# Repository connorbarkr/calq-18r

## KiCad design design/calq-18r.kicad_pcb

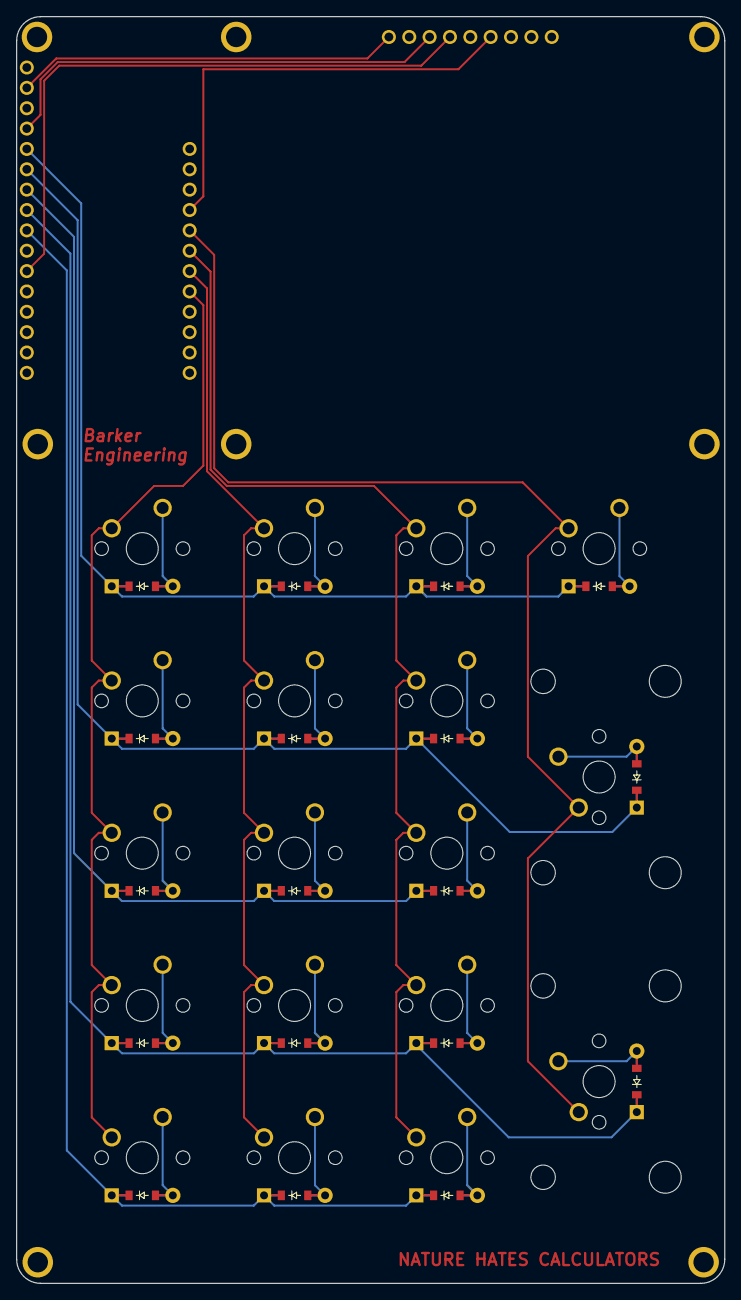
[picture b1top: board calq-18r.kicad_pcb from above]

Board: 2 copper layers, 88.4 x 158.1 mm, 40 parts (0 on the bottom side), 31 nets.

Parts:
D1, D2, D3, D4, D5, D6, D7, D8, D9, D10, D11, D12, D13, D14, D15, D16, D17, D18: ComboDiode
DISP1: DISP; SHARP_2_7
MCU1: Feather_nRF52840
S1, S2, S3, S4, S5, S6, S7, S8, S9, S10, S11, S12, S13, S14, S15, S16, S17, S18: MX
Stab1, Stab2: MX_stabilizer

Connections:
A0: D5.1, D5.2, D10.1, D10.2, D15.1, D15.2, D18.1, D18.2, MCU1.17
A1: D4.1, D4.2, D9.1, D9.2, D14.1, D14.2, D17.1, D17.2, MCU1.18
A2: D3.1, D3.2, D8.1, D8.2, D13.1, D13.2, MCU1.19
A3: D2.1, D2.2, D7.1, D7.2, D12.1, D12.2, D16.1, D16.2, MCU1.20
A4: D1.1, D1.2, D6.1, D6.2, D11.1, D11.2, MCU1.21
D9: MCU1.8, S1.2, S2.2, S3.2, S4.2, S5.2
D10: MCU1.7, S6.2, S7.2, S8.2, S9.2, S10.2
D11: MCU1.6, S11.2, S12.2, S13.2, S14.2, S15.2
D12: MCU1.5, S16.2, S17.2, S18.2
D13: DISP1.6, MCU1.4
GND: DISP1.3, MCU1.16
RAW: DISP1.1, MCU1.14
SCK: DISP1.4, MCU1.23
d_A_a: D5.1, D5.2, S5.1
d_A_b: D4.1, D4.2, S4.1
d_A_c: D3.1, D3.2, S3.1
d_A_d: D2.1, D2.2, S2.1
d_A_e: D1.1, D1.2, S1.1
d_B_a: D10.1, D10.2, S10.1
d_B_b: D9.1, D9.2, S9.1
d_B_c: D8.1, D8.2, S8.1
d_B_d: D7.1, D7.2, S7.1
d_B_e: D6.1, D6.2, S6.1
d_C_a: D15.1, D15.2, S15.1
d_C_b: D14.1, D14.2, S14.1
d_C_c: D13.1, D13.2, S13.1
d_C_d: D12.1, D12.2, S12.1
d_C_e: D11.1, D11.2, S11.1
d_D_a: D18.1, D18.2, S18.1
d_D_b: D17.1, D17.2, S17.1
d_D_d: D16.1, D16.2, S16.1

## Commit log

2022-06-03 initial commit: created PCB
2022-06-03 readme
2022-06-07 basic infix calculator functional
